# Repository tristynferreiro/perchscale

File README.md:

# The Hornbill Sensor Project
Project still in progress

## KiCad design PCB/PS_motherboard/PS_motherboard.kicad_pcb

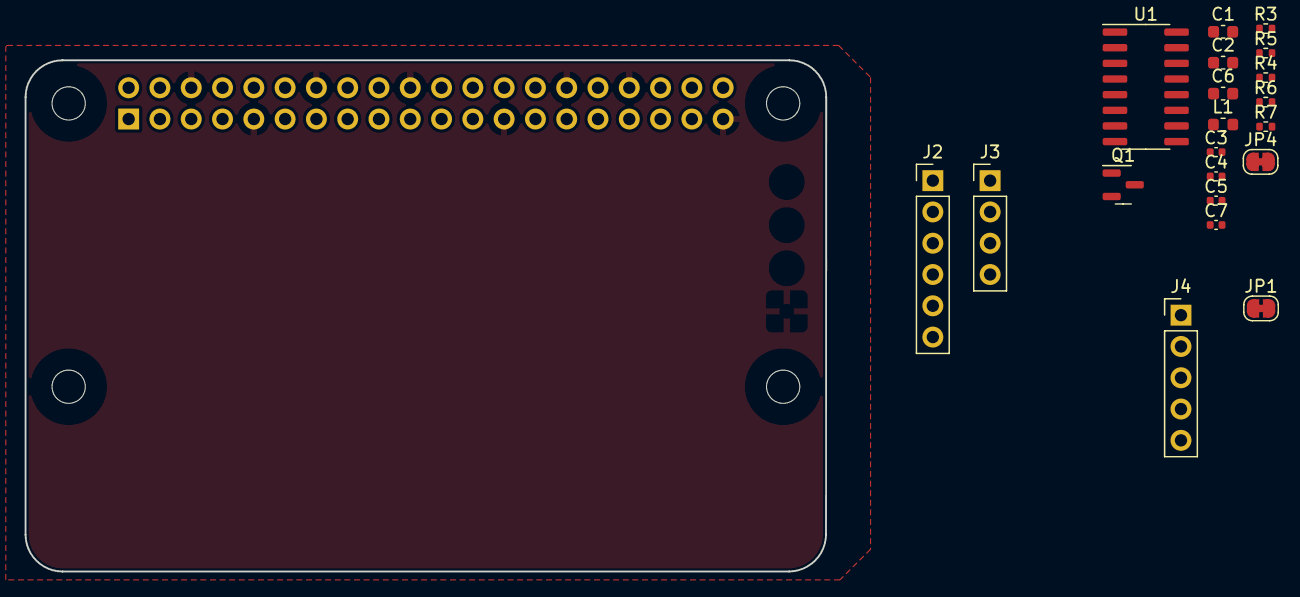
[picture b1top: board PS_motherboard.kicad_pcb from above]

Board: 2 copper layers, 65.0 x 41.5 mm, 25 parts (1 on the bottom side), 19 nets, no tracks yet.

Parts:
C1: 100n; C_0603_1608Metric
C2, C6: 10u; C_0603_1608Metric
C3, C4, C5, C7: 100n; C_0402_1005Metric
H1, H2, H3, H4: MountingHole; MountingHole_2.7mm_M2.5_uHAT_RPi
J2: Conn_01x06_Socket; PinHeader_1x06_P2.54mm_Vertical
J3: Conn_01x04_Socket; PinHeader_1x04_P2.54mm_Vertical
J4: Conn_01x05_Pin; PinHeader_1x05_P2.54mm_Vertical
J5: GPIO_CONNECTOR; PinSocket_2x20_P2.54mm_Vertical_Centered_Anchor
JP1, JP4: RATE; SolderJumper-2_P1.3mm_Bridged_RoundedPad1.0x1.5mm
L1: 3.3uH; L_0603_1608Metric
Q1: S8550; SOT-23
R3, R4: 100R; R_0402_1005Metric
R5: 12k; R_0402_1005Metric
R6: 27k; R_0402_1005Metric
R7: 10k; R_0402_1005Metric
U1: HX711; SOP-16_3.9x9.9mm_P1.27mm

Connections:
+3.3V: C5.1, J4.1, J5.1, J5.17, U1.16 (DVDD)
+5V: C6.1, C7.1, J3.1, J5.2, J5.4, Q1.3 (C), R7.2, U1.1 (VSUP)
/EXC+: C1.1, C2.1, J2.1, L1.1
/GPIO2_SDA1: J4.2, J5.3
/GPIO3_SCL1: J4.3, J5.5
/GPIO5: J3.3, J5.29, U1.12 (DOUT)
/GPIO6: J3.4, J5.31, U1.11 (PD_SCK)
/INA+: J2.4, R3.1
/INA-: J2.3, R4.1
/INB+: J2.6, U1.9 (INB-)
/INB-: J2.5, U1.10 (INB+)
GND: C1.2, C2.2, C4.2, C5.2, C6.2, C7.2, J2.2, J3.2, J4.5, J5.6, J5.9, J5.14, J5.20, J5.25, J5.30, J5.34, J5.39, JP1.1 (A), JP4.1 (A), R5.1, U1.5 (AGND), U1.14 (XI)
unnamed: JP1.2 (B), R7.1, U1.15 (RATE)
unnamed: Q1.1 (B), U1.2 (BASE)
unnamed: L1.2, Q1.2 (E), R6.1, U1.3 (AVDD)
unnamed: C3.1, R3.2, U1.8 (INA+)
unnamed: C3.2, R4.2, U1.7 (INA-)
unnamed: C4.1, U1.6 (VBG)
unnamed: R5.2, R6.2, U1.4 (VFB)

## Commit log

2023-04-15 Added datasheets
2023-04-15 Added .DS_Store to .gitignore
2023-04-15 Removed .DS_Store
2023-04-15 Added TP4056 voltage regulator datasheet
2023-04-15 Scale Calibration Base Code
2023-04-15 Added scale HX711.h file
2023-04-15 Added HX711X Library to be imported into Arduino IDE to use the scale code
2023-04-15 Arduino test code
2023-04-15 Updated Calibration Code to work on ESP32
2023-04-15 Wireless Network: Working webserver test
2023-04-15 Updated Software Readme
2023-04-17 Added Webserver creation project
2023-04-22 interim PCB design
2023-04-22 Added arduino files for scale
2023-04-22 Updated Wifi code
2023-04-22 Fixed Tristyn's Disaster
2023-04-22 Added SSID to data transfer project
2023-04-22 Changed from using wifi server to webserver
2023-04-22 Testing SD Card Files
2023-04-27 Organising files
2023-04-27 Added basic SD Card interfacing project
2023-04-27 Some horse shit
2023-04-27 Test file download from webserver
2023-04-27 Mishay's calibration code
2023-04-30 Added comments
2023-04-30 UART data sending test code
2023-04-30 Tristyn's UART Sauce
2023-04-30 Receive data oveer UART and write to SD card
2023-04-30 Project files for scale and data transfer integration
2023-04-30 Added scale code to sender
2023-04-30 Updated UART sender code with scale stuff
2023-04-30 Sending Scale Data over UARTgit add .git add .
2023-05-04 Added array scale reading project
2023-05-05 Updated almost perfect business
2023-05-13 Added UART scale testing project
2023-05-13 Updated Scale UART program
2023-05-17 The business/working scale code
2023-05-17 Renaming files
2023-05-17 File renaming
2023-05-18 Module diagrams added
2023-05-18 powerpoint presentation
2024-02-02 Add 4113F Folder and first interface with scale
2024-02-02 Added the stl file for Perch Box V7
2024-02-07 Created the Calibration.py file
2024-02-07 Reorganised the github
2024-02-07 Camera - simple script to capture still images and save them to files
2024-02-07 Creating a scale script that writes readings to readings.txt
2024-02-07 Camera - simple script to capture video and save to files
2024-02-07 Create rtc script
2024-02-16 RTC implementation to get time at desired intervals and write to txt file
2024-02-16 Added filtering code using Kalman Filter
2024-02-16 Added ability to write optimal parameters to file
2024-03-22 Added Motherboard PCB files
2024-03-22 Updated LCSC part numbers and footprints for all parts EXCEPT PB and Screw Terminals (added comments why not)
2024-03-25 Update footprints
2024-03-29 ESP32: added new scale reading code
2024-03-29 ESP32: working scale script with calibration, and printing to serial
2024-03-29 ESP32: working scale code that writes to serial output
2024-03-29 Added serialReader script
2024-04-05 Testing folder added
2024-04-12 RTC: added working interfacing script between Pi RTC and ESP32
2024-04-12 Added H-bar perch design
2024-04-12 initial commit of perchdesign_tbar_v1
2024-04-12 Scale: timestamped weighing code
2024-04-12 Deleted .gcode files for old perch and box designs
2024-04-18 Update screw hole size on hbar to 3.8mm for M4 screws
2024-04-18 Updated full and shortened hperch design to have longer screw holes (50mm)
2024-04-19 Replace .stl files for hbar designs with .step files
2024-04-19 Initial commit of test screw .step for determining correct print size of screw holes
2024-04-19 housing step files
2024-04-19 Scale: Working - Integrated SD card file writing code
2024-04-26 Scale: added two load cell script
2024-04-26 Documentation: datasheets
2024-04-26 Rename twoloadcells to twoHX711s and update code to take in two HX711 inputs on the same clock line
2024-05-03 Rename hperch files to nperch because it was actually n-shaped not h-shaped
2024-05-03 Scale: saves to sdcard once buffer is full - buffersize can be adjusted
2024-05-03 Cleaning
2024-05-30 Scale: updated print messages for easy debugging
2024-06-07 Scale: Attempt to implement N-perch
2024-06-07 Added script template
2024-06-07 Added Tbar housing v3
2024-06-07 Display: Hello World scripts for OLED and LCD WORKING
2024-06-07 BLE: Hellow world server script working
2024-06-07 Display: output live weight readings from load cell
2024-06-07 DPAD: Working function to detect state of all 4 butotns and display on OLED display
2024-06-07 Scale: integrated bleserver with basic scale reading script
2024-06-07 Menu: Created script to interface with menu using DPAD (Not working)
2024-06-14 Added T-Perch Design with embedded OLED
2024-06-15 OLED: Added inital menu function
2024-06-15 OLED: Update menu code to include delays correctly between process screens
2024-06-15 general code cleaning
2024-06-15 OLED MENU: Update comments and improve readability
2024-06-15 Upload correct u8g2 library
2024-06-24 Controller: BLE client code integration with menu on OLED
2024-06-24 Upload server code for controller
2024-06-28 Scale: integrating ble server code (still in progress)
2024-06-28 Scale: Initial commit of update to scale readings on OLED using u8g2 library
2024-06-28 Remove scale code from housing branch
2024-07-05 BLE server + controller: added some calibration functionality
2024-07-26 Controller & Scale: Save calibration factor to EEPROM for 200g and update controller screens to display saving process correctly
2024-08-07 Added Controller PCB Folder with the Power Circuitry
2024-08-07 Added CAD models for controller under Housing
2024-08-07 Added all the step modules for components in the controller
2024-08-08 Controller PCB: Initial schematic design. Added schematic for status LEDs & pins for exisiting connections
2024-10-11 Scale: Successfully integrated bleserver code with scale. Still no calibration code.
2024-10-11 Scale: Integrating sd card, incomplete
2024-10-11 Scale: Integrated RTC with scale code. No working calibration solution yet
2024-10-21 SD card: attempt at adding calibration file
2024-10-21 Controller: Updated menu to have disconnect functionality.
2024-10-21 Calibration: save calibration values to file on SD card
2024-10-21 Controller: Added disconnect feature, which works with menu screens
2024-10-21 Scale: added save to SD card when device disconnects
2024-10-21 Controller: Update calibration scheme to be 5 point and include change mass values closer to be closer to SYBH values
2024-10-23 Scale: File paths are named using RTC reading and updated every hour. Added additional accepted calibration weights. Other minor updates and cleaning.
2024-10-24 Controller and Scale: Updated calibration procedure to facilitate 7 calibration points.
2024-10-24 Scale: added a function for updating the file path name every hour
2024-10-24 Cleaned up print lines and display screens.
2024-10-29 Controller: added DPAD pin state variables
2024-10-29 Controller: renamed file
2024-10-29 Cleaning for v1 deployment
2024-10-29 Changed the buttons to be PULLUP and operate on a low level
2024-10-30 Scale: added conditional definition for OLED. Start of log file code
2024-10-30 Tristyn asked me to push
2024-10-30 Scale: cleaning up the code, added some functions for data logging
2024-10-30 changed calibration weights
2024-10-30 Scale: cleaning the calibration function
2024-10-30 Scale: bug fix, buffer over flow
2024-10-31 Scale: cleaning, integrating controller modes with logData() function
2024-10-31 Scale: Log messages added
2024-11-01 Scale: added calibration factor calculation and set
2024-11-01 Calibration: changed to 3 point calibration
2024-11-01 Scale: updated calibration procedure and how the reading threshold is set
2024-11-01 Scale: stopped using tareNoDelay()
2024-11-01 Interrim updates
2024-11-01 Scale: threshold bug fix, restructure and cleaning.
2024-11-04 Controller: Add Disable BLE screen and update menu flow
2024-11-04 Scale: cleaning and adding comments
2024-11-04 BLE: added a disable functionality to both the controller and scale. bug fix on tare always failing
2024-11-21 Added my code with changes that worked in field testing
2024-12-06 BUG FIX: Fixed the bug that was causing the calibration factor to be reset when the controller is connected
2024-12-06 Added if defines for serial comms (debug mode) and added calibration values for big birds
2024-12-06 Updated controller and scale code with 10kg/20kg loadcell calibration values
